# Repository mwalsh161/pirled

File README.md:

# PIR LED Controllers

Design goals:
1. A single ESP8266 governs up to 4 LEDs + 4 PIR sensors (+4 virtual signals).
2. Any LED can trigger on/off with any grouping of PIR sensors/virtual signals.
    - Note, logical OR with each other hard-coded.
    - Each LED can have a delay associated with certain triggerers.
3. Discoverable through MDNS.
    - Service name begins with "pirled-controller"
    - Signed firmeware uploadable by Arduino OTA.
4. Config is controllable in realtime, and supports fairly aggressive polling rates.
5. No network should not prohibit core detect/dimming functionality.
    - Note, plan to allow sharing sensors...obviously that isn't included here (e.g. not making )

TODO:
1. When updating something, returning the binary app state in response can drastically cut down
   on requests (requires more complex JS logic, but that's fine).
2. Layers are currently pretty heavily tied to arduino/esp. Makes unit-testing harder.
    - Goal: leverage templates + shims to make a test build possible on non-esp hosts.
3. Sharing sensors
4. Robust to network outages (e.g. rebind as part of state machine).
    - note reboot is an easy way to do this, but given some GPIO pin activity during boot this would
      be less than ideal.
    - it would require re-"beginning" all server objects including mdns and maybe arduino ota.
    - would need same logic as setup to effectively switch to the portal

Stretch TODO:
1. ESP AP mode allows multiple to link together to continue allowing sharing sensors without network
    - what is AP range?
    - would need a "house" key to validate connecting. No security + no SSL...big yikes
    - ...maybe not.

## PlatformIO cache setup

This project uses a repo-local PlatformIO core directory at `.platformio-core/` so VS Code builds and CLI builds can share the same cache and incremental build context.

If you already have PlatformIO packages installed globally in `~/.platformio`, you can optionally symlink these into `.platformio-core/` to avoid re-downloading toolchains and frameworks:

```sh
ln -s ~/.platformio/packages .platformio-core/packages
ln -s ~/.platformio/platforms .platformio-core/platforms
```

This is optional. If the symlinks are absent, PlatformIO can manage `.platformio-core/` directly.

## Docker deployment

The API server can be built as a single production image that also contains the built frontend bundle. Build from the repo root so the Docker build can access both `api/` and `frontend/`:

```sh
docker build -f api/Dockerfile -t pirled:latest .
```

Run it with a bind mount or named volume for persistent app state at `/data` and publish port `8082`:

```sh
docker run --rm \
  -p 8082:8082 \
  -v "$(pwd)/api-data:/data" \
  pirled:latest
```

Notes:
- The image builds `frontend/dist` during `docker build`; no prebuilt frontend artifact is required.
- Persistent data is intentionally excluded from the image and should be mounted at `/data` so host backup/restore jobs can access it.
- The runtime data path can be overridden with `PIRLED_DATA_DIR`; local non-Docker runs default to `api/data`.
- Existing deploys that already mount `/app/api/data` can either move that host directory to the `/data` mount or set `PIRLED_DATA_DIR=/app/api/data`.
- The frontend already uses relative asset and API paths, which keeps it compatible with subpath deployments.

For a homelab deploy repo, the expected invocation is:

```sh
git clone <this-repo>
cd pirled
docker build -f api/Dockerfile -t pirled:latest .
docker run -d \
  --name pirled \
  --restart unless-stopped \
  -p 8082:8082 \
  -v /path/to/persistent/pirled-data:/data \
  pirled:latest
```

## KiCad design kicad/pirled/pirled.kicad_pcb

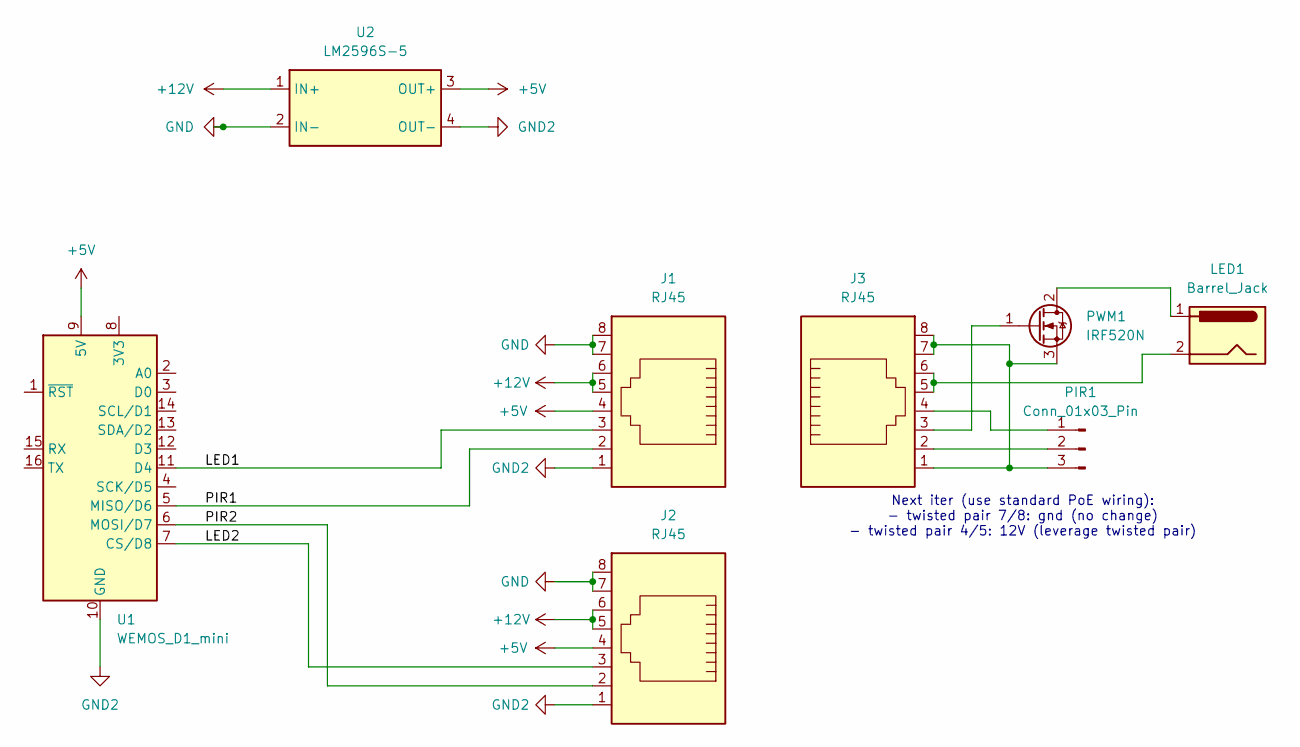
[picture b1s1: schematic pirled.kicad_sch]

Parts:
J1, J2, J3: RJ45; RJ45_breakout
LED1: Barrel_Jack; BarrelJack_SwitchcraftConxall_RAPC10U_Horizontal
PIR1: Conn_01x03_Pin; PinHeader_1x03_P1.00mm_Vertical
PWM1: IRF520N; TO-220-3_Vertical
U1: WEMOS_D1_mini; WEMOS_D1_mini_light
U2: LM2596S-5; Converter_DCDC_LM2596

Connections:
+5V: J1.4, J2.4, U1.9 (5V), U2.3 (OUT+)
+12V: J1.5, J1.6, J2.5, J2.6, U2.1 (IN+)
/LED1: J1.3, U1.11 (D4)
/LED2: J2.3, U1.7 (CS/D8)
/PIR1: J1.2, U1.5 (MISO/D6)
/PIR2: J2.2, U1.6 (MOSI/D7)
GND: J1.7, J1.8, J2.7, J2.8, U2.2 (IN-)
GND2: J1.1, J2.1, U1.10 (GND), U2.4 (OUT-)
unnamed: J3.5, J3.6, LED1.2
unnamed: J3.4, PIR1.1
unnamed: J3.2, PIR1.2
unnamed: J3.1, J3.7, J3.8, PIR1.3, PWM1.3 (S)
unnamed: LED1.1, PWM1.2 (D)
unnamed: J3.3, PWM1.1 (G)

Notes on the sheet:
Next iter (use standard PoE wiring): - twisted pair 7/8: gnd (no change) - twisted pair 4/5: 12V (leverage twisted pair)

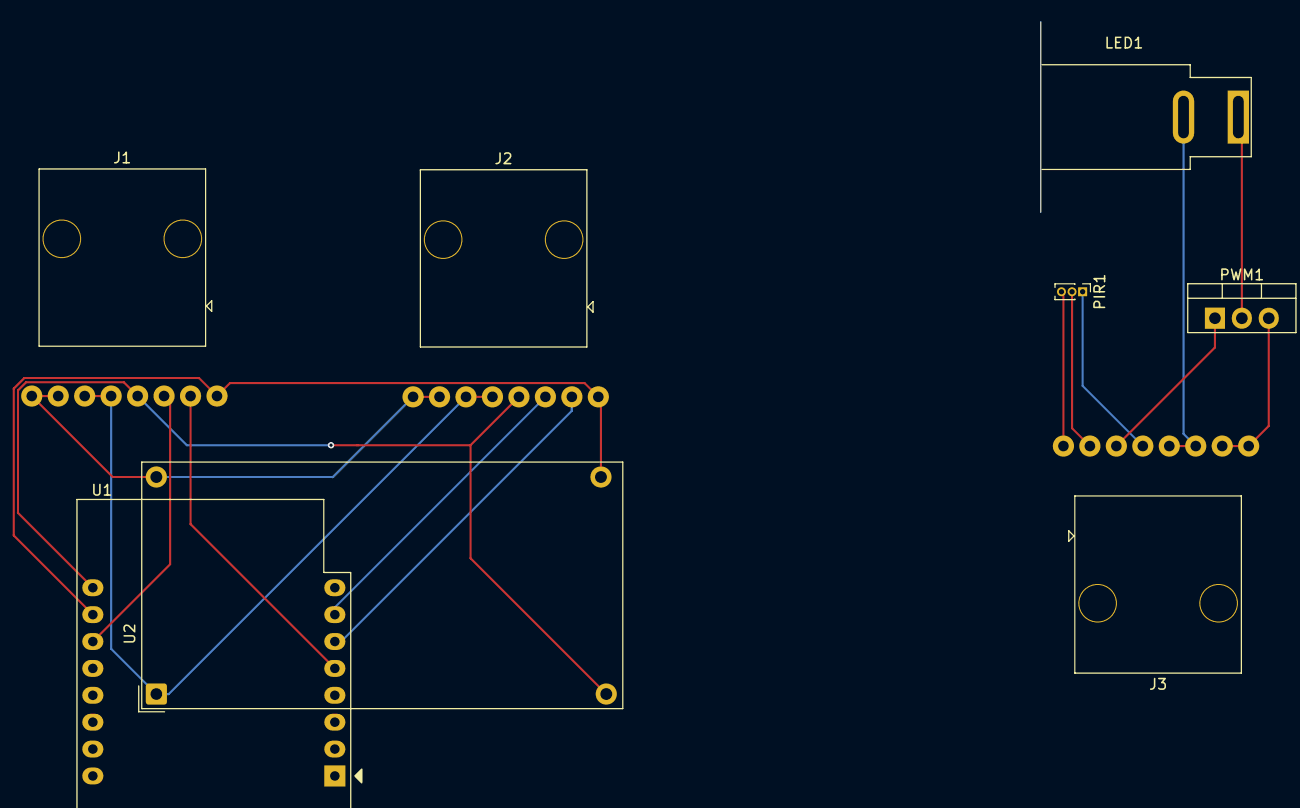
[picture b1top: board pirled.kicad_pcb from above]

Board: 2 copper layers, 8 parts (0 on the bottom side), 14 nets.

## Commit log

2026-01-03 format
2026-01-03 refactor led cntl and simplify wifi creds
2026-01-04 state machine for the win again
2026-01-04 encapsulate controller logic
2026-01-06 move setup to cpp
2026-01-07 add multiple independent controllers
2026-01-07 decouple led ctl and sense
2026-01-07 add serial api for configuring masks
2026-01-07 add fetch capability
2026-01-15 add in config and control server
2026-01-15 add mdns
2026-01-16 add virtual pir
2026-01-16 add status endpoint
2026-01-16 add CORS
2026-01-17 add a SPA
2026-01-17 slider instead of text
2026-01-17 configurable port and launch script
2026-01-19 serialize esp fetch batch
2026-01-19 cont update on slide
2026-01-19 fix mobile size
2026-01-21 arduino OTA
2026-01-21 use mdns service name instead of text record
2026-01-24 overhaul Led and up; patch bugs in server/client; add logger/debug tools
2026-01-24 add kicad
2026-01-24 slim down html and separate templating dom from value updating
2026-01-24 shuffle globals around to AppState
2026-01-25 switch to binary protocol
2026-01-25 fix enum size in binary
2026-01-26 Add delay on parameter
2026-01-26 use different pir mask for on vs off
2026-01-31 more robust wifi handling
2026-01-31 remove blocking wifi logic to main loop
2026-01-31 handle multiple controllers
2026-01-31 add jitter
2026-02-01 add firmware version by commit; leverage post requests to replace polling
2026-02-06 improve firmware versioning
2026-02-11 firmware: validate config inputs, encapsulate state access, and clean up internal linkage
2026-02-22 Convert to a react app and add persisting config framework
2026-02-22 fix unsigned error; no save debounce; use rtc mem for double and tripple tap resets; more reseed and restart in wifi state machine
2026-02-23 chore: checkpoint decoupled discovery and resolve baseline
2026-02-23 feat(live): restore group collapse and visible-device polling
2026-02-23 refactor(api): unify alias and label cleaning pipeline
2026-02-23 fix resolution flag in label matrix
2026-02-23 add preview/edit for moods
2026-02-23 moods folder
2026-02-23 scheduler introduced
2026-02-24 re-org server
2026-02-25 refactor(api): make mood apply label resolution always return a set
2026-02-25 feat(workspace): add persisted setup/live/moods tabs and setup state in localStorage
2026-02-25 feat(live-controls): handle unresolved devices and simplify LED endpoint config UI
2026-02-25 feat(mood-studio): lazy-load mood data, gate polling to moods tab, and redesign schedules panel
2026-02-25 Refactor workspace polling and streamline label matrix UX
2026-02-25 use volta instead of conda for node
2026-04-12 no reboots while retrying wifi; explicit portal mode
2026-04-13 npm version bumps; use rel paths to avoid rev proxy issues
2026-05-02 Keep fade updates free of per-step logging
2026-05-02 Prioritize LED updates in the main loop
2026-05-02 Expose runtime LED state through read-only accessors
2026-05-02 Extract reset-tap boot handling
2026-05-02 Organize firmware sources by subsystem
2026-05-02 Rename board and runtime state headers
2026-05-02 Split config store from config server
2026-05-02 Extract WiFi manager implementation
2026-05-02 Normalize firmware include style
2026-05-02 Fix reset reason debug format
2026-05-02 Widen PIR masks to 16 bits
2026-05-02 Add remote PIR runtime state
2026-05-02 Add remote PIR sharing config
2026-05-02 Receive remote PIR events over UDP
2026-05-02 Send remote PIR events over UDP
2026-05-02 Add remote sensor sharing UI
2026-05-02 add migrated config
2026-05-03 expose firmware version
2026-05-03 better initial load flow to use cache unless user needs to explicitly have server refresh
2026-05-03 add timestamps to logs
2026-05-03 hard-code udp port for sensor sharing
2026-05-03 refactor frontend to be more intuitive with remote sensors
2026-05-03 Handle partial remote sharing loads
2026-05-03 Add boot-time WiFi reseed recovery
2026-05-03 Add persistent boot history diagnostics
2026-05-03 Try earlier config versions during migration
2026-05-03 Reserve legacy config space before boot history
2026-05-03 Simplify WiFi retry flow after DHCP testing
    Extensive testing pointed away from our application-level recovery logic and toward an ESP8266 SDK DHCP client issue. Static IP succeeded immediately, while auto-reseed, portal-style rewrites, radio 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
    Given that result, this change removes the heavier warm/cold retry state machine and keeps only a lightweight periodic reattach loop for ordinary network hiccups. Wrong-password remains terminal unti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
2026-05-03 Require static WiFi network config on ESP8266
    Persist static IP settings outside the versioned app config and collect them through the setup portal.
    Remove the boot-time WiFi reseed path and keep reconnect behavior lightweight after testing showed the ESP8266 SDK DHCP client can associate and receive offers without completing requests.
    Add a 3-tap LED warning window so the following tap is required before wiping stored WiFi/static network settings.
2026-05-04 Auto-open portal for static network transition
    Add a firmware-controlled portal latch for the DHCP-to-static-IP transition. The latch is intentionally based only on network state: no manual tap sequence, stored WiFi credentials present, and no st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
    Record firmware-triggered portal boots in boot history so the migration path is visible during field testing.
2026-05-04 share build cache with agents
2026-05-04 tighten up cors handling to one layer (and fix remote_pir cors issue)
2026-05-04 Improve remote PIR mdns handling and logging
2026-05-04 Detect and repair remote broadcast drift
2026-05-10 Add Docker deployment support
2026-05-11 Add Docker healthcheck endpoint
2026-05-25 Use daily wall-clock mood schedules
    Replace interval-based mood schedules with HH:MM server-local schedules. Compute nextRunAt from timeOfDay instead of persisting it, reject legacy schedule fields, and update the Mood Studio UI/API pa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
2026-05-25 Resolve devices by hostname when mDNS service data is missing
    Add a default device HTTP port and fall back to resolving <device>.local via getaddrinfo when cached mDNS service info is unavailable or lacks an IPv4 address.
2026-05-25 expose data dir from docker image
